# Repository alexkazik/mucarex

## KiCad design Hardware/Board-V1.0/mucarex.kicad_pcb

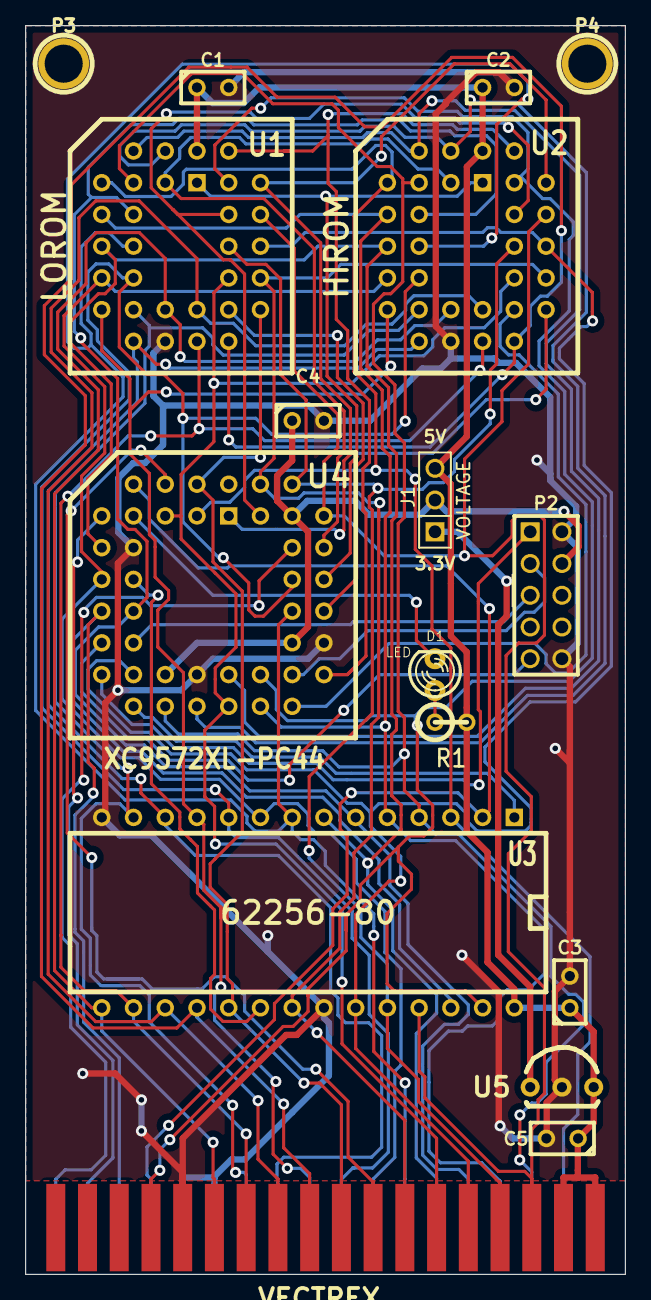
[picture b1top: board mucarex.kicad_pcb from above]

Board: 2 copper layers, 48.0 x 99.9 mm, 17 parts (0 on the bottom side), 48 nets.

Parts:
C1, C2, C3, C4: 0.1uF; C1
C5: 4,7uF; C1
D1: LED; LED-3MM
J1: VOLTAGE; PIN_ARRAY_3X1
P1: VECTREX; VECTREX-EDGE
P2: PROG; PIN_ARRAY_5x2
P3, P4: CONN_1; 1pin
R1: 75; R1
U1: LOROM; PLCC32
U2: HIROM; PLCC32
U3: 62256-80; DIP-28__600
U4: XC9572XL-PC44; PLCC44
U5: TS2950; TO-92-Free-inline-wide

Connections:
/VREG: J1.1, U5.1
A0: P1.17, U1.12, U2.12, U3.10, U4.36
A1: P1.15, U1.11, U2.11, U3.9, U4.11
A2: P1.13, U1.10, U2.10, U3.8, U4.34
A3: P1.11, U1.9, U2.9, U3.7, U4.9
A4: P1.9, U1.8, U2.8, U3.6, U4.14
A5: P1.7, U1.7, U2.7, U3.5, U4.26
A6: P1.5, U1.6, U2.6, U3.4, U4.20
A7: P1.3, U1.5, U2.5, U3.3, U4.3
A8: P1.6, U1.27, U2.27, U3.25, U4.39
A9: P1.8, U1.26, U2.26, U3.24, U4.40
A10: P1.14, U1.23, U2.23, U3.21, U4.42
A11: P1.10, U1.25, U2.25, U3.23, U4.19
A12: P1.29, U3.2, U4.6
A13: P1.31, U3.26, U4.13
A14: P1.33, U4.7
A15: P1.16, U4.4
D0: P1.19, U1.13, U2.13, U3.11
D1: P1.21, U1.14, U2.14, U3.12
D2: P1.23, U1.15, U2.15, U3.13
D3: P1.26, U1.17, U2.17, U3.15
D4: P1.24, U1.18, U2.18, U3.16
D5: P1.22, U1.19, U2.19, U3.17
D6: P1.20, U1.20, U2.20, U3.18
D7: P1.18, U1.21, U2.21, U3.19, U4.2
F1CE: U1.22, U4.33
F2CE: U2.22, U4.28
FA12: U1.4, U2.4, U4.25
FA13: U1.28, U2.28, U4.43
FA14: U1.29, U2.29, U4.1
FA15: U1.3, U2.3, U4.37
FA16: U1.2, U2.2, U4.22
FA17: U1.30, U2.30, U4.29
FA18: U1.1, U2.1, U4.35
GND: C1.2, C2.2, C3.2, C4.2, C5.2, P1.25, P1.27, P1.28, P2.2, P2.10, P3.1, P4.1, U1.16, U2.16, U3.14, U3.22, U4.10, U4.23, U4.31, U5.2
LED: D1.2, U4.8
unnamed: D1.1, R1.1
OE: P1.12, U1.24, U2.24, U4.5, U4.24
PB6: P1.35, U4.38
RA14: U3.1, U4.18
RCE: U3.20, U4.12
RW: P1.30, U1.31, U2.31, U3.27, U4.27
TCK: P2.1, U4.17
TDI: P2.9, U4.15
TDO: P2.3, U4.30
TMS: P2.5, U4.16
VCC: C1.1, C2.1, C3.1, C5.1, J1.3, P1.2, P1.4, R1.2, U1.32, U2.32, U3.28, U5.3
VCPLD: C4.1, J1.2, P2.4, U4.21, U4.32, U4.41

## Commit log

2014-09-03 First public release
2014-11-04 cleanup and optimization

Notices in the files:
Hardware/Board-V1.0/mucarex.kicad_pcb:
(C)2014 P1X3L.NET
